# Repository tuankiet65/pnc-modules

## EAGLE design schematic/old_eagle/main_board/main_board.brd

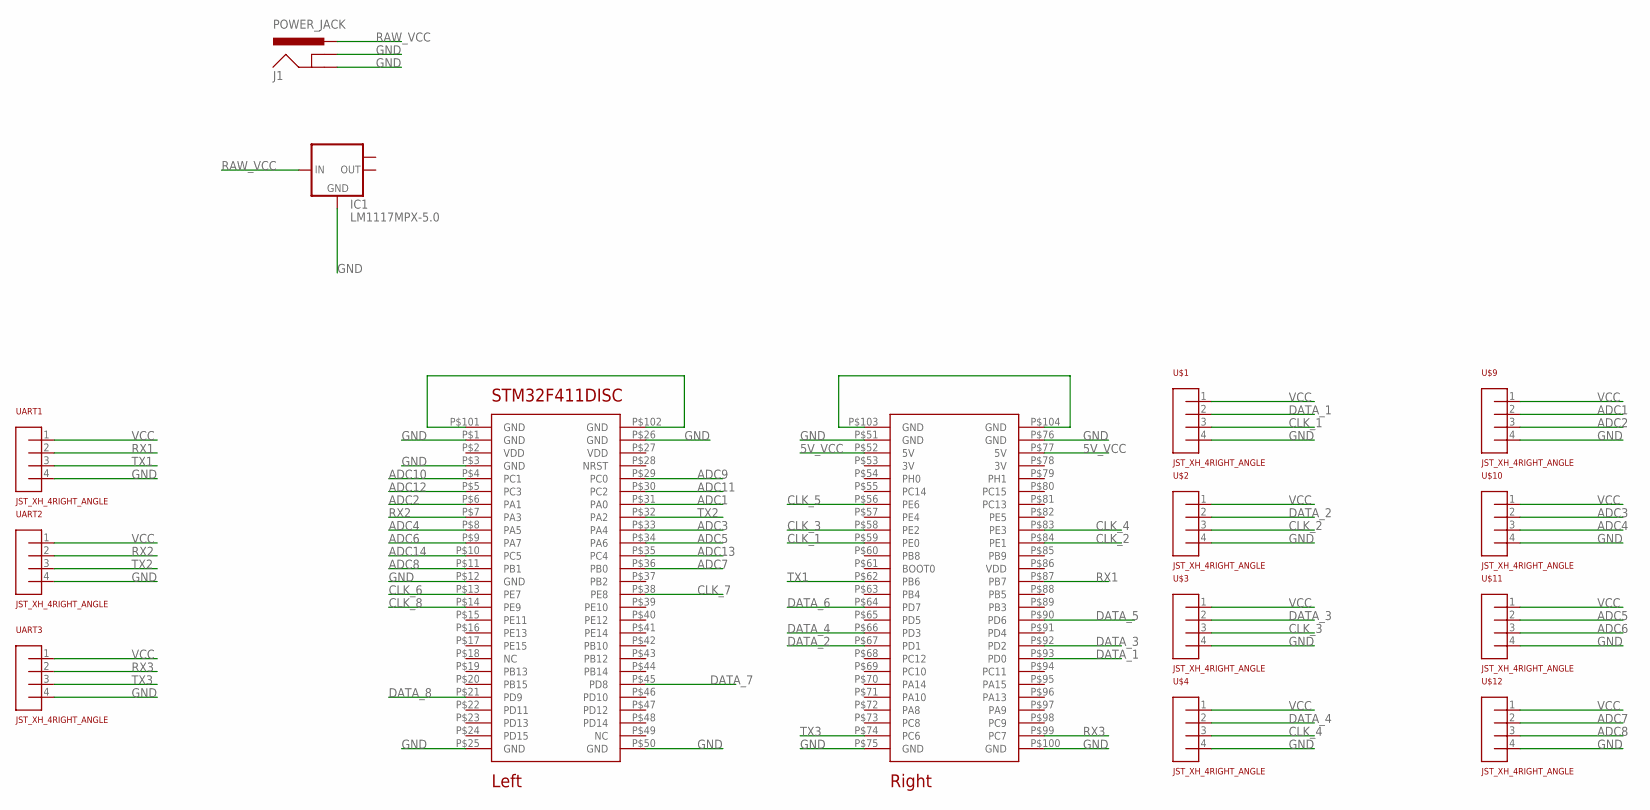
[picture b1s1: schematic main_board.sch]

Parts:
IC1: LM1117MPX-5.0; SOT223
J1: POWER_JACK; POWER_JACK_PTH
STM32F411DISC: STM32F411_DISCOVERY
U$1, U$2, U$3, U$4, U$9, U$10, U$11, U$12: JST_XH_4RIGHT_ANGLE; JST_XH_4PIN_RIGHT_ANGLE
UART1, UART2, UART3: JST_XH_4RIGHT_ANGLE; JST_XH_4PIN_RIGHT_ANGLE

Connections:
5V_VCC: STM32F411DISC.P$52 (5V), STM32F411DISC.P$77 (5V)
ADC1: STM32F411DISC.P$31 (PA0), U$9.2
ADC2: STM32F411DISC.P$6 (PA1), U$9.3
ADC3: STM32F411DISC.P$33 (PA4), U$10.2
ADC4: STM32F411DISC.P$8 (PA5), U$10.3
ADC5: STM32F411DISC.P$34 (PA6), U$11.2
ADC6: STM32F411DISC.P$9 (PA7), U$11.3
ADC7: STM32F411DISC.P$36 (PB0), U$12.2
ADC8: STM32F411DISC.P$11 (PB1), U$12.3
ADC9: STM32F411DISC.P$29 (PC0)
ADC10: STM32F411DISC.P$4 (PC1)
ADC11: STM32F411DISC.P$30 (PC2)
ADC12: STM32F411DISC.P$5 (PC3)
ADC13: STM32F411DISC.P$35 (PC4)
ADC14: STM32F411DISC.P$10 (PC5)
CLK_1: STM32F411DISC.P$59 (PE0), U$1.3
CLK_2: STM32F411DISC.P$84 (PE1), U$2.3
CLK_3: STM32F411DISC.P$58 (PE2), U$3.3
CLK_4: STM32F411DISC.P$83 (PE3), U$4.3
CLK_5: STM32F411DISC.P$56 (PE6)
CLK_6: STM32F411DISC.P$13 (PE7)
CLK_7: STM32F411DISC.P$38 (PE8)
CLK_8: STM32F411DISC.P$14 (PE9)
DATA_1: STM32F411DISC.P$93 (PD0), U$1.2
DATA_2: STM32F411DISC.P$67 (PD1), U$2.2
DATA_3: STM32F411DISC.P$92 (PD2), U$3.2
DATA_4: STM32F411DISC.P$66 (PD3), U$4.2
DATA_5: STM32F411DISC.P$90 (PD6)
DATA_6: STM32F411DISC.P$64 (PD7)
DATA_7: STM32F411DISC.P$45 (PD8)
DATA_8: STM32F411DISC.P$21 (PD9)
GND: IC1.1 (GND), J1.GND, J1.GNDBREAK, STM32F411DISC.P$1 (GND), STM32F411DISC.P$3 (GND), STM32F411DISC.P$12 (GND), STM32F411DISC.P$25 (GND), STM32F411DISC.P$26 (GND), STM32F411DISC.P$50 (GND), STM32F411DISC.P$51 (GND), STM32F411DISC.P$75 (GND), STM32F411DISC.P$76 (GND), STM32F411DISC.P$100 (GND), U$1.4, U$2.4, U$3.4, U$4.4, U$9.4, U$10.4, U$11.4, U$12.4, UART1.4, UART2.4, UART3.4
unnamed: STM32F411DISC.P$103 (GND), STM32F411DISC.P$104 (GND)
unnamed: STM32F411DISC.P$101 (GND), STM32F411DISC.P$102 (GND)
RAW_VCC: IC1.3 (IN), J1.PWR
RX1: STM32F411DISC.P$87 (PB7), UART1.2
RX2: STM32F411DISC.P$7 (PA3), UART2.2
RX3: STM32F411DISC.P$99 (PC7), UART3.2
TX1: STM32F411DISC.P$62 (PB6), UART1.3
TX2: STM32F411DISC.P$32 (PA2), UART2.3
TX3: STM32F411DISC.P$74 (PC6), UART3.3
VCC: U$1.1, U$2.1, U$3.1, U$4.1, U$9.1, U$10.1, U$11.1, U$12.1, UART1.1, UART2.1, UART3.1

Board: 2 copper layers, 14 parts (0 on the bottom side), 28 nets, no tracks yet.

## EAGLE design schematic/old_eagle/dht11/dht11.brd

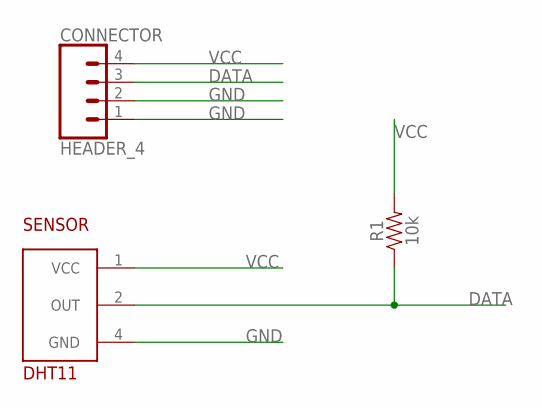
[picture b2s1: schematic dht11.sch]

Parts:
CONNECTOR: HEADER_4; MOLEX-1X4
R1: 10k; AXIAL-0.3
SENSOR: DHT11

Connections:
DATA: CONNECTOR.3, R1.P$1 (1), SENSOR.2 (OUT)
GND: CONNECTOR.1, CONNECTOR.2, SENSOR.4 (GND)
VCC: CONNECTOR.4, R1.P$2 (2), SENSOR.1 (VCC)

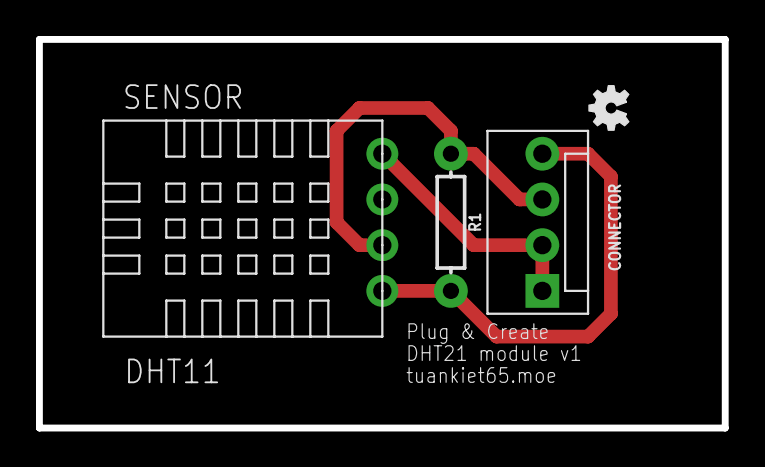
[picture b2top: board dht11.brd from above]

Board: 2 copper layers, 38.1 x 21.6 mm, 4 parts (0 on the bottom side), 3 nets.

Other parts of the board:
U$1: OSHW-LOGO-MINI

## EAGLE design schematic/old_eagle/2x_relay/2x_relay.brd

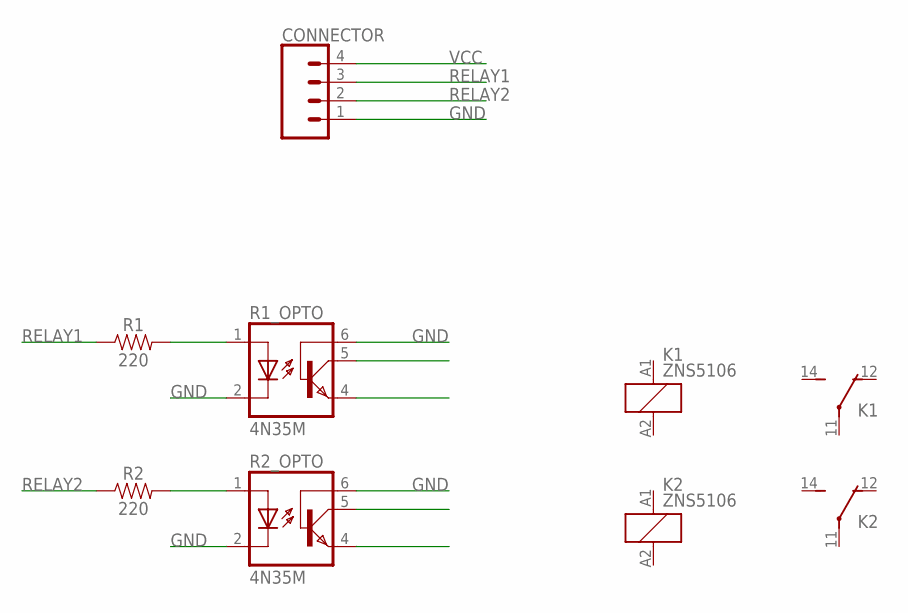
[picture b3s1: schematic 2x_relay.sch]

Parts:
CONNECTOR: CONN_04POLAR; MOLEX-1X4
K1, K2: ZNS5106; ZN5
R1, R2: 220; AXIAL-0.3
R1_OPTO, R2_OPTO: 4N35M; DIL06

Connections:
GND: CONNECTOR.1, R1_OPTO.2 (C), R1_OPTO.6 (BAS), R2_OPTO.2 (C), R2_OPTO.6 (BAS)
unnamed: R1.P$2 (2), R1_OPTO.1 (A)
unnamed: R2.P$2 (2), R2_OPTO.1 (A)
RELAY1: CONNECTOR.3, R1.P$1 (1)
RELAY2: CONNECTOR.2, R2.P$1 (1)
VCC: CONNECTOR.4

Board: 2 copper layers, 7 parts (0 on the bottom side), 5 nets, no tracks yet.

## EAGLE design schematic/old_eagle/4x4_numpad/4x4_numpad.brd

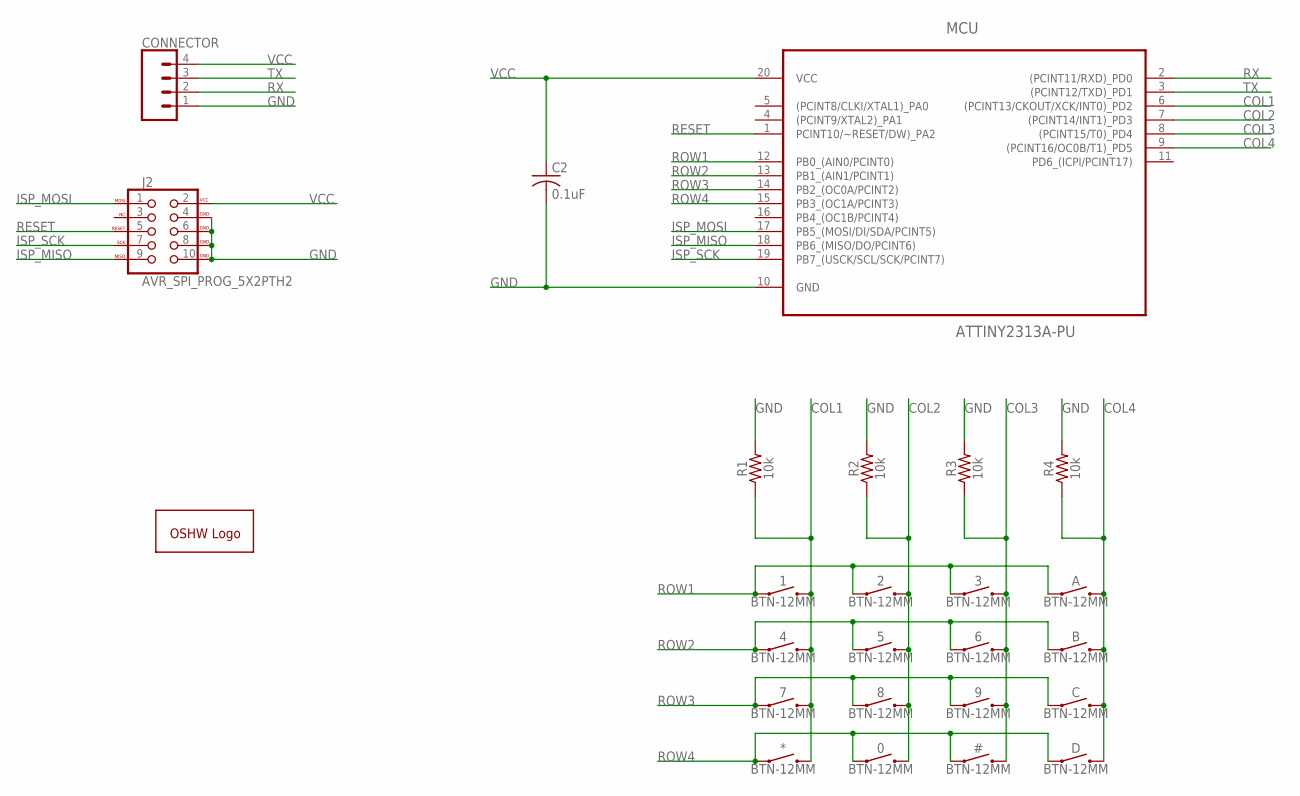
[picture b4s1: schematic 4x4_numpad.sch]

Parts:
0, 1, 2, 3, 4, 5, 6, 7, 8, 9: BTN-12MM; TACTILE_SWITCH_PTH_12MM
#: BTN-12MM; TACTILE_SWITCH_PTH_12MM
*: BTN-12MM; TACTILE_SWITCH_PTH_12MM
A: BTN-12MM; TACTILE_SWITCH_PTH_12MM
B: BTN-12MM; TACTILE_SWITCH_PTH_12MM
C: BTN-12MM; TACTILE_SWITCH_PTH_12MM
C2: 0.1uF; C050-025X075
CONNECTOR: CONN_04; 1X04
D: BTN-12MM; TACTILE_SWITCH_PTH_12MM
GOLD_ORB_SM1: OSHWLOGOLOGO8MM; OSHW_8MM
J2: AVR_SPI_PROG_5X2PTH2; 2X5-SHROUDED
MCU: ATTINY2313A-PU; DIP254P762X533-20
R1, R2, R3, R4: 10k; AXIAL-0.3

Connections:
COL1: 1.3 (2), 1.4 (2), 4.3 (2), 4.4 (2), 7.3 (2), 7.4 (2), *.3 (2), *.4 (2), MCU.6 ((PCINT13/CKOUT/XCK/INT0)_PD2), R1.P$1 (1)
COL2: 0.3 (2), 0.4 (2), 2.3 (2), 2.4 (2), 5.3 (2), 5.4 (2), 8.3 (2), 8.4 (2), MCU.7 ((PCINT14/INT1)_PD3), R2.P$1 (1)
COL3: 3.3 (2), 3.4 (2), 6.3 (2), 6.4 (2), 9.3 (2), 9.4 (2), #.3 (2), #.4 (2), MCU.8 ((PCINT15/T0)_PD4), R3.P$1 (1)
COL4: A.3 (2), A.4 (2), B.3 (2), B.4 (2), C.3 (2), C.4 (2), D.3 (2), D.4 (2), MCU.9 ((PCINT16/OC0B/T1)_PD5), R4.P$1 (1)
GND: C2.2, CONNECTOR.1, J2.4 (GND), J2.6 (GND), J2.8 (GND), J2.10 (GND), MCU.10 (GND), R1.P$2 (2), R2.P$2 (2), R3.P$2 (2), R4.P$2 (2)
ISP_MISO: J2.9 (MISO), MCU.18 (PB6_(MISO/DO/PCINT6))
ISP_MOSI: J2.1 (MOSI), MCU.17 (PB5_(MOSI/DI/SDA/PCINT5))
ISP_SCK: J2.7 (SCK), MCU.19 (PB7_(USCK/SCL/SCK/PCINT7))
RESET: J2.5 (RESET), MCU.1 (PCINT10/~RESET/DW)_PA2)
ROW1: 1.1, 1.2 (1), 2.1, 2.2 (1), 3.1, 3.2 (1), A.1, A.2 (1), MCU.12 (PB0_(AIN0/PCINT0))
ROW2: 4.1, 4.2 (1), 5.1, 5.2 (1), 6.1, 6.2 (1), B.1, B.2 (1), MCU.13 (PB1_(AIN1/PCINT1))
ROW3: 7.1, 7.2 (1), 8.1, 8.2 (1), 9.1, 9.2 (1), C.1, C.2 (1), MCU.14 (PB2_(OC0A/PCINT2))
ROW4: 0.1, 0.2 (1), #.1, #.2 (1), *.1, *.2 (1), D.1, D.2 (1), MCU.15 (PB3_(OC1A/PCINT3))
RX: CONNECTOR.2, MCU.2 ((PCINT11/RXD)_PD0)
TX: CONNECTOR.3, MCU.3 ((PCINT12/TXD)_PD1)
VCC: C2.1, CONNECTOR.4, J2.2 (VCC), MCU.20 (VCC)

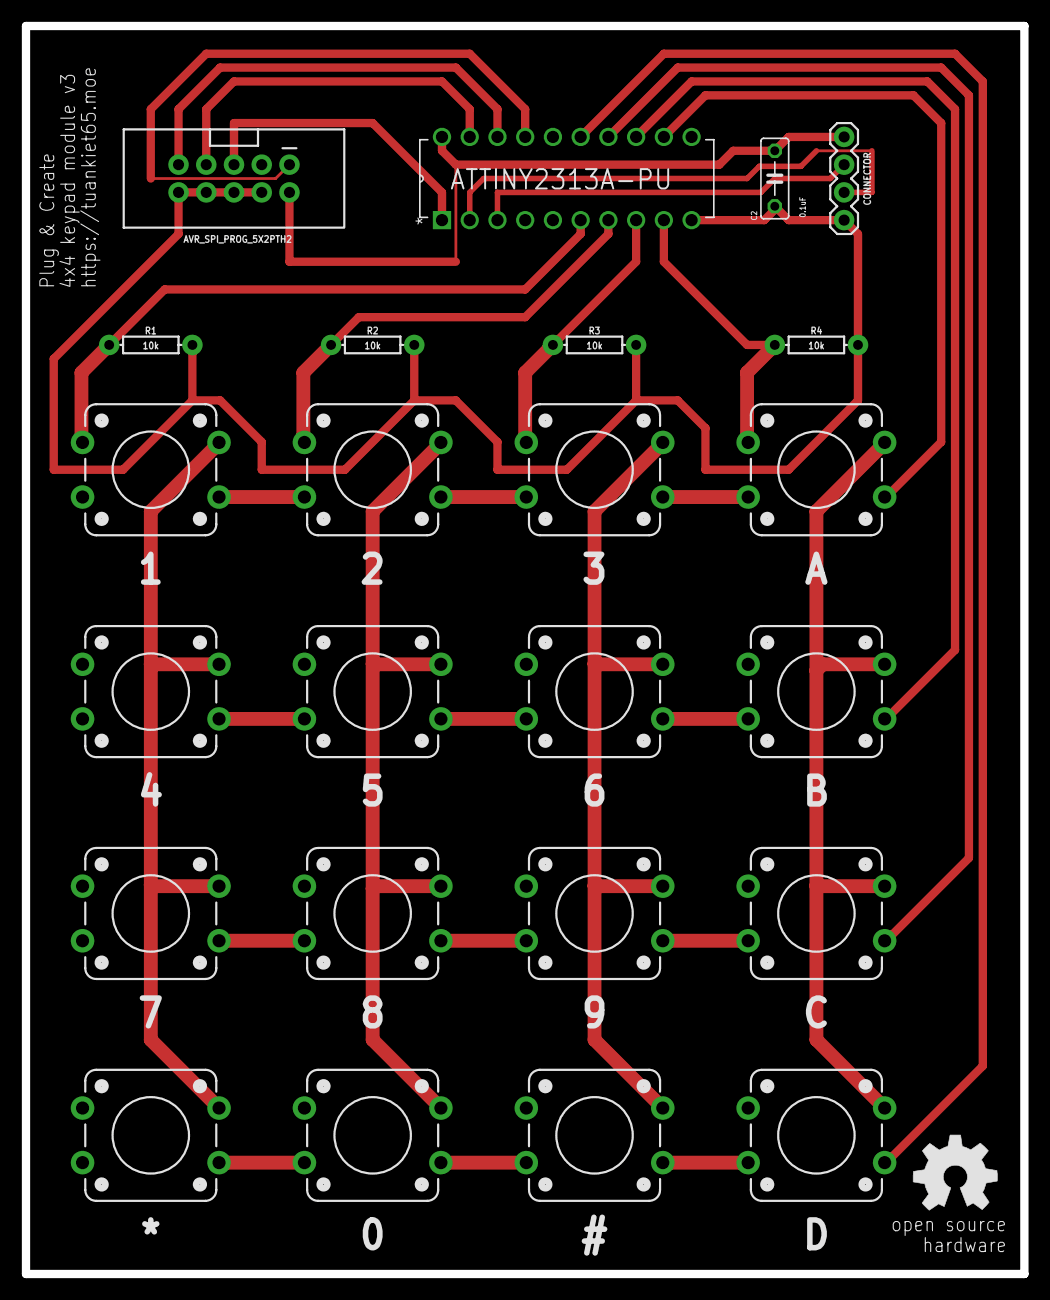
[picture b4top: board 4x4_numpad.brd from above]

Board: 2 copper layers, 91.4 x 114.3 mm, 25 parts (0 on the bottom side), 16 nets.

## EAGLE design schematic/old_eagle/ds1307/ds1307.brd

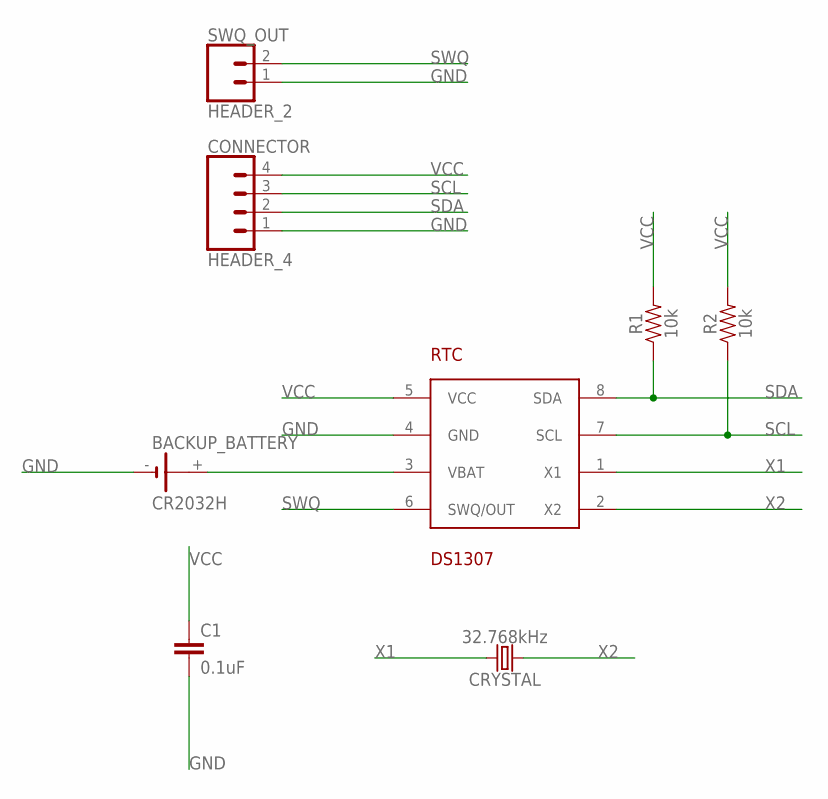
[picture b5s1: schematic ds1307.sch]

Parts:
BACKUP_BATTERY: CR2032H
C1: 0.1uF; CAP-PTH-SMALL-KIT
CONNECTOR: HEADER_4; MOLEX-1X4
CRYSTAL: 32.768kHz; CRYSTAL-PTH-2X6-CYL
R1, R2: 10k; AXIAL-0.3
RTC: DS1307; MAXIM_DIP8
SWQ_OUT: HEADER_2; 1X02

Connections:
GND: BACKUP_BATTERY.-, C1.2, CONNECTOR.1, RTC.4 (GND), SWQ_OUT.1
unnamed: BACKUP_BATTERY.+, RTC.3 (VBAT)
SCL: CONNECTOR.3, R2.P$1 (1), RTC.7 (SCL)
SDA: CONNECTOR.2, R1.P$1 (1), RTC.8 (SDA)
SWQ: RTC.6 (SWQ/OUT), SWQ_OUT.2
VCC: C1.1, CONNECTOR.4, R1.P$2 (2), R2.P$2 (2), RTC.5 (VCC)
X1: CRYSTAL.2, RTC.1 (X1)
X2: CRYSTAL.1, RTC.2 (X2)

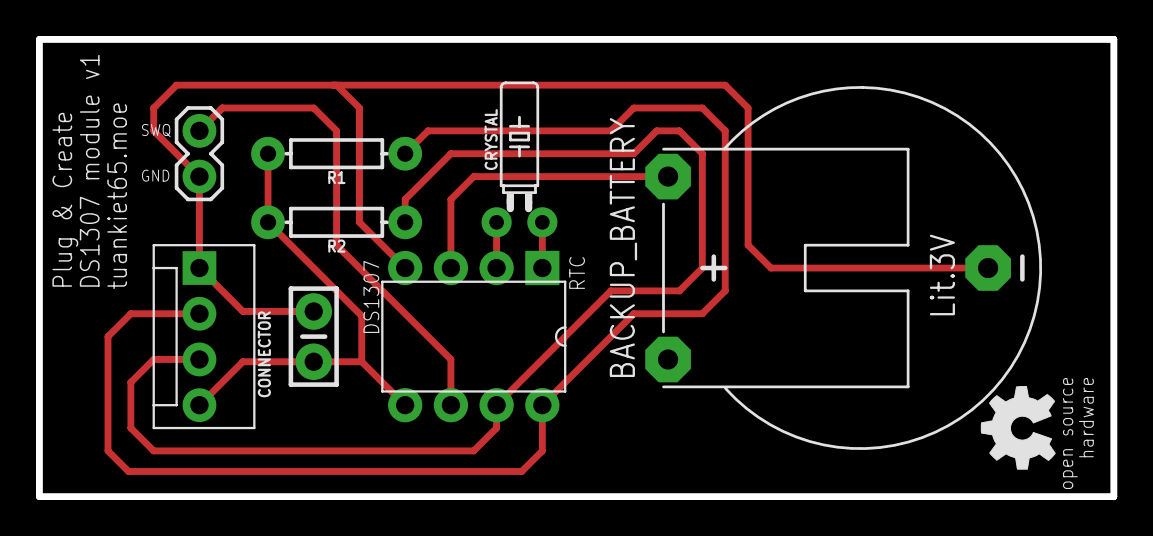
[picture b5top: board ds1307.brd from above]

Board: 2 copper layers, 59.7 x 25.4 mm, 9 parts (0 on the bottom side), 8 nets.

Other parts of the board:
U$1: OSHW_5MM

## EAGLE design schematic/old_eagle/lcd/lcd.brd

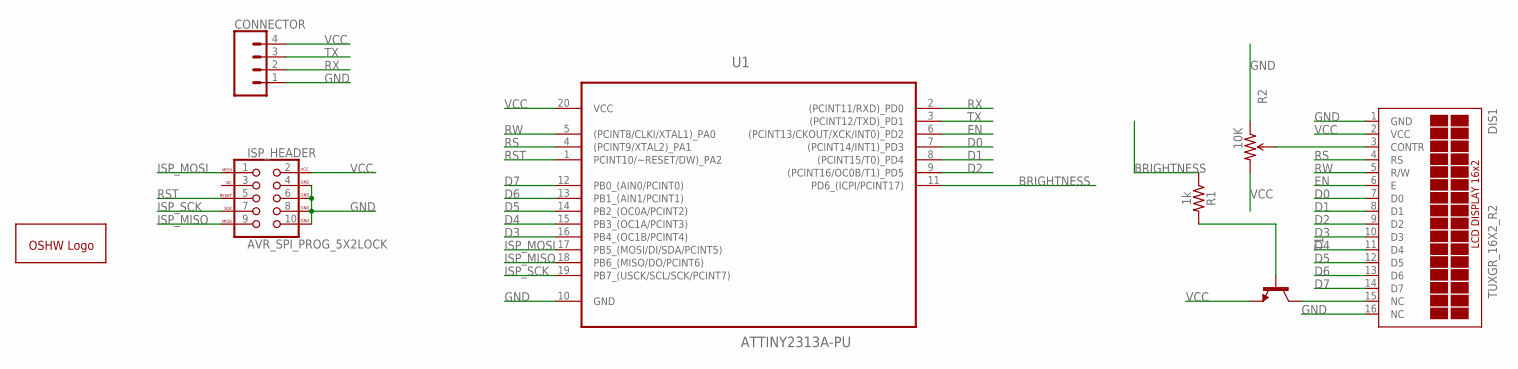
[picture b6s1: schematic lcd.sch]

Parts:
CONNECTOR: CONN_04; 1X04
DIS1: TUXGR_16X2_R2
GOLD_ORB_SM2: OSHWLOGOLOGO5MM; OSHW_5MM
ISP_HEADER: AVR_SPI_PROG_5X2LOCK; 2X5-SHROUDED_LOCK
R1: 1k; AXIAL-0.3
R2: 10K; TRIM_POT_PTH
T1: -NPN-TO92-ECB; TO92-ECB
U1: ATTINY2313A-PU; DIP254P762X533-20

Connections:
BRIGHTNESS: R1.P$1 (1), U1.11 (PD6_(ICPI/PCINT17))
CONTRAST: DIS1.3 (CONTR), R2.2 (WIPER)
D0: DIS1.7 (D0), U1.7 ((PCINT14/INT1)_PD3)
D1: DIS1.8 (D1), U1.8 ((PCINT15/T0)_PD4)
D2: DIS1.9 (D2), U1.9 ((PCINT16/OC0B/T1)_PD5)
D3: DIS1.10 (D3), U1.16 (PB4_(OC1B/PCINT4))
D4: DIS1.11 (D4), U1.15 (PB3_(OC1A/PCINT3))
D5: DIS1.12 (D5), U1.14 (PB2_(OC0A/PCINT2))
D6: DIS1.13 (D6), U1.13 (PB1_(AIN1/PCINT1))
D7: DIS1.14 (D7), U1.12 (PB0_(AIN0/PCINT0))
EN: DIS1.6 (E), U1.6 ((PCINT13/CKOUT/XCK/INT0)_PD2)
GND: CONNECTOR.1, DIS1.1 (GND), DIS1.16 (NC), ISP_HEADER.4 (GND), ISP_HEADER.6 (GND), ISP_HEADER.8 (GND), ISP_HEADER.10 (GND), R2.1 (CCW), U1.10 (GND)
ISP_MISO: ISP_HEADER.9 (MISO), U1.18 (PB6_(MISO/DO/PCINT6))
ISP_MOSI: ISP_HEADER.1 (MOSI), U1.17 (PB5_(MOSI/DI/SDA/PCINT5))
ISP_SCK: ISP_HEADER.7 (SCK), U1.19 (PB7_(USCK/SCL/SCK/PCINT7))
unnamed: DIS1.15 (NC), T1.C
unnamed: R1.P$2 (2), T1.B
RS: DIS1.4 (RS), U1.4 ((PCINT9/XTAL2)_PA1)
RST: ISP_HEADER.5 (RESET), U1.1 (PCINT10/~RESET/DW)_PA2)
RW: DIS1.5 (R/W), U1.5 ((PCINT8/CLKI/XTAL1)_PA0)
RX: CONNECTOR.2, U1.2 ((PCINT11/RXD)_PD0)
TX: CONNECTOR.3, U1.3 ((PCINT12/TXD)_PD1)
VCC: CONNECTOR.4, DIS1.2 (VCC), ISP_HEADER.2 (VCC), R2.3 (CW), T1.E, U1.20 (VCC)

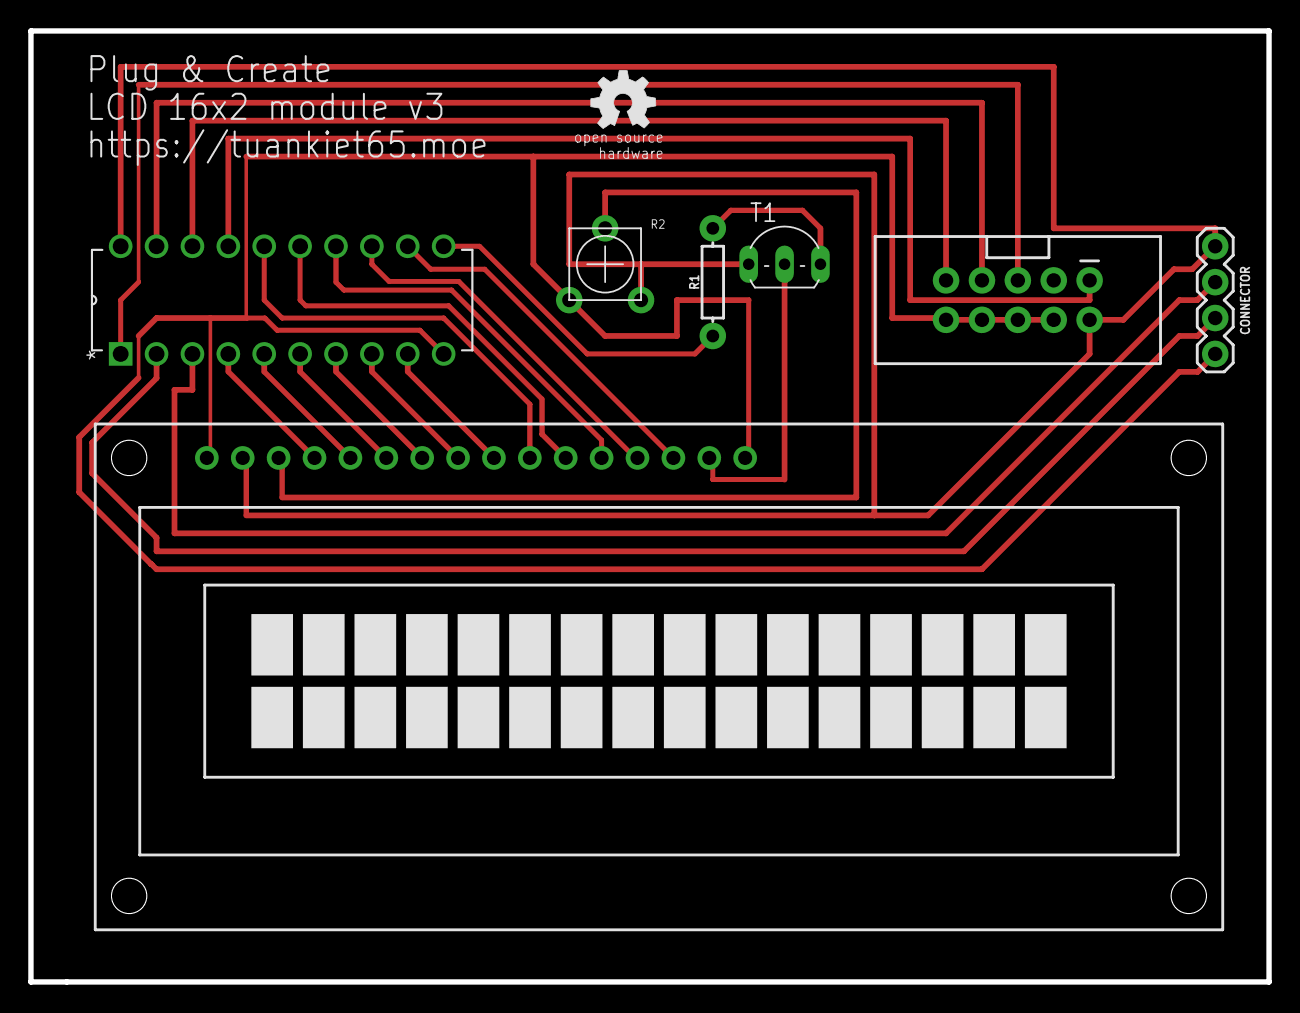
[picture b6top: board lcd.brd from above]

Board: 2 copper layers, 87.6 x 67.3 mm, 8 parts (0 on the bottom side), 23 nets.

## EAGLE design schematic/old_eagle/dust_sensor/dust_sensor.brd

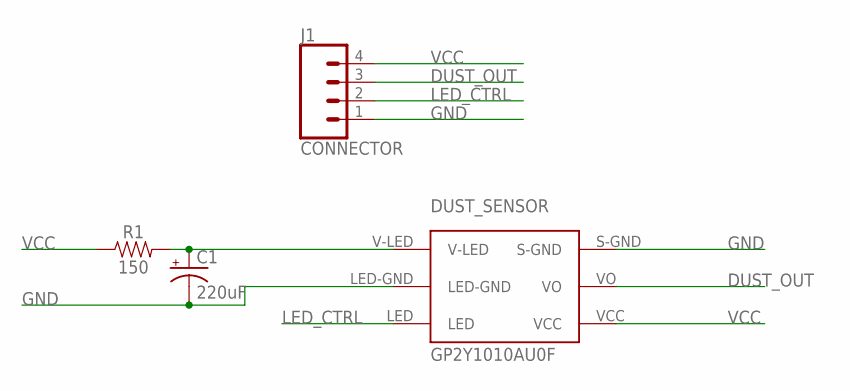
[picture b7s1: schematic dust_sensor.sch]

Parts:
C1: 220uF; E2,5-6
DUST_SENSOR: GP2Y1010AU0F
J1: CONNECTOR; MOLEX-1X4
R1: 150; AXIAL-0.3

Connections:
DUST_OUT: DUST_SENSOR.VO, J1.3
GND: C1.-, DUST_SENSOR.LED-GND, DUST_SENSOR.S-GND, J1.1
LED_CTRL: DUST_SENSOR.LED, J1.2
unnamed: C1.+, DUST_SENSOR.V-LED, R1.P$2 (2)
VCC: DUST_SENSOR.VCC, J1.4, R1.P$1 (1)

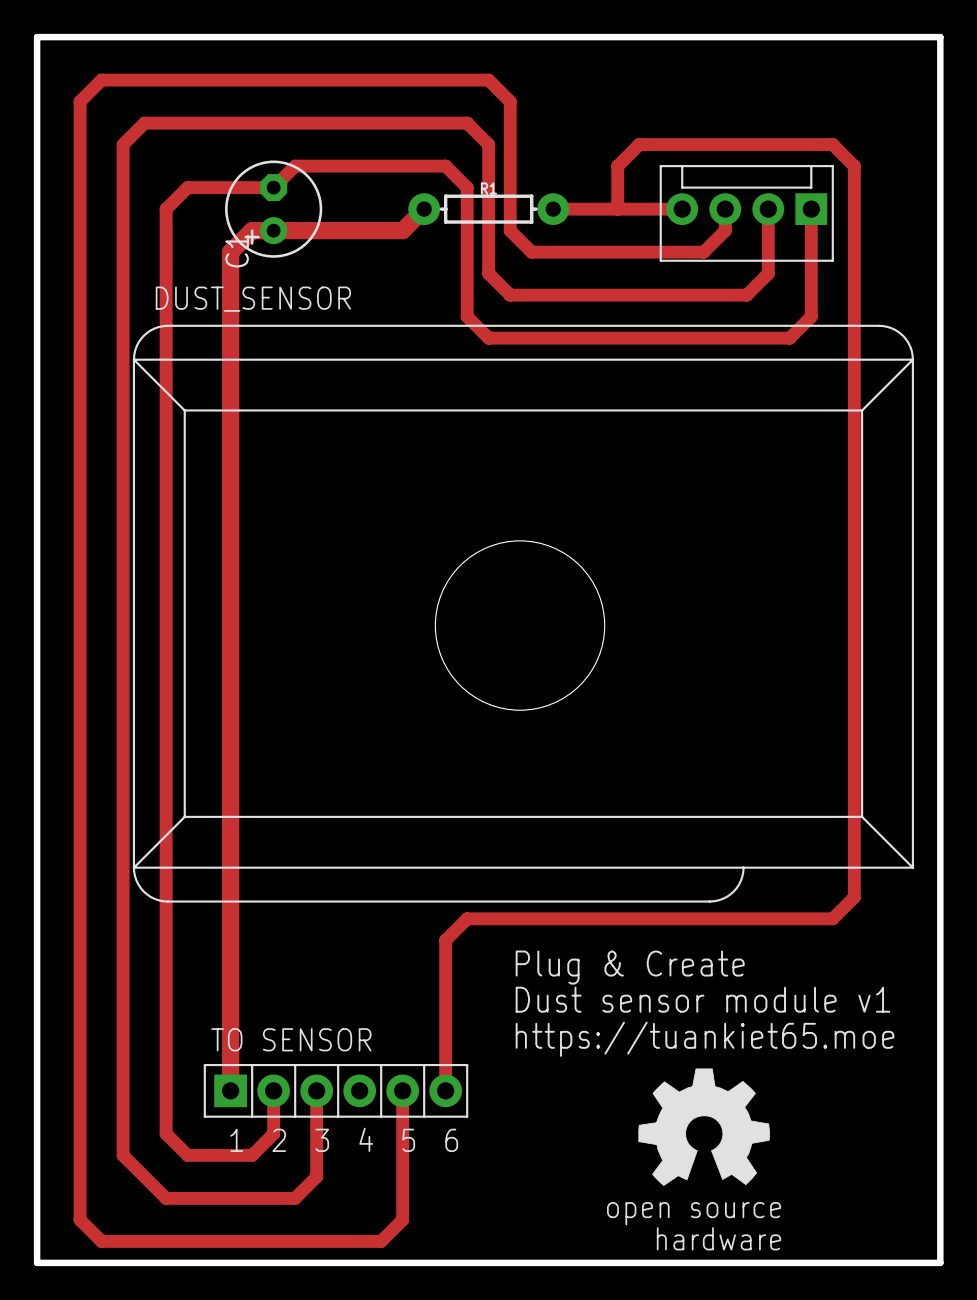
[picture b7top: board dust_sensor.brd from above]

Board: 2 copper layers, 53.3 x 72.4 mm, 5 parts (0 on the bottom side), 5 nets.

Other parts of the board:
U$1: OSHW_8MM

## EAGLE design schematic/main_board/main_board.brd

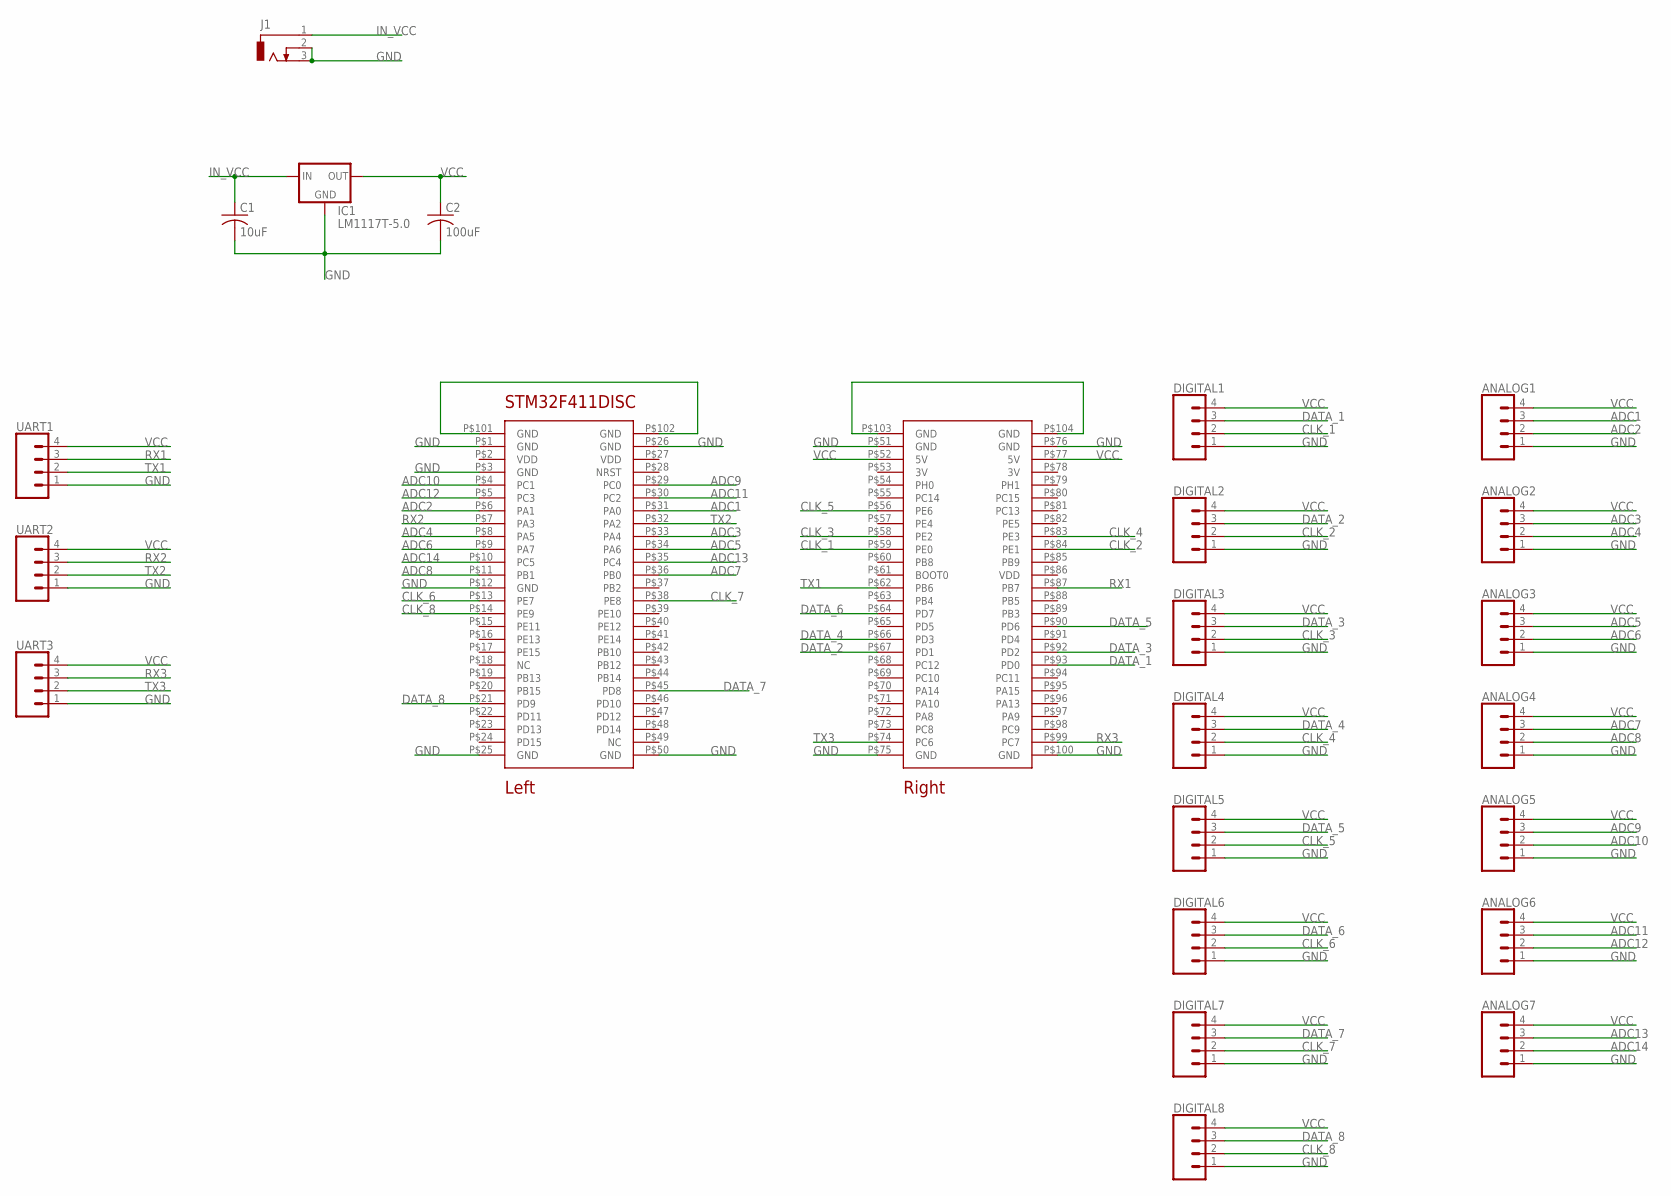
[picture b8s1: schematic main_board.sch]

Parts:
ANALOG1, ANALOG2, ANALOG3, ANALOG4, ANALOG5, ANALOG6, ANALOG7: CONN_04; 1X04
C1: 10uF; C025-025X050
C2: 100uF; C025-025X050
DIGITAL1, DIGITAL2, DIGITAL3, DIGITAL4, DIGITAL5, DIGITAL6, DIGITAL7, DIGITAL8: CONN_04; 1X04
IC1: LM1117T-5.0; TO220
J1: DCJ0303
STM32F411DISC: STM32F411_DISCOVERY
UART1, UART2, UART3: CONN_04; 1X04

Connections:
ADC1: ANALOG1.3, STM32F411DISC.P$31 (PA0)
ADC2: ANALOG1.2, STM32F411DISC.P$6 (PA1)
ADC3: ANALOG2.3, STM32F411DISC.P$33 (PA4)
ADC4: ANALOG2.2, STM32F411DISC.P$8 (PA5)
ADC5: ANALOG3.3, STM32F411DISC.P$34 (PA6)
ADC6: ANALOG3.2, STM32F411DISC.P$9 (PA7)
ADC7: ANALOG4.3, STM32F411DISC.P$36 (PB0)
ADC8: ANALOG4.2, STM32F411DISC.P$11 (PB1)
ADC9: ANALOG5.3, STM32F411DISC.P$29 (PC0)
ADC10: ANALOG5.2, STM32F411DISC.P$4 (PC1)
ADC11: ANALOG6.3, STM32F411DISC.P$30 (PC2)
ADC12: ANALOG6.2, STM32F411DISC.P$5 (PC3)
ADC13: ANALOG7.3, STM32F411DISC.P$35 (PC4)
ADC14: ANALOG7.2, STM32F411DISC.P$10 (PC5)
CLK_1: DIGITAL1.2, STM32F411DISC.P$59 (PE0)
CLK_2: DIGITAL2.2, STM32F411DISC.P$84 (PE1)
CLK_3: DIGITAL3.2, STM32F411DISC.P$58 (PE2)
CLK_4: DIGITAL4.2, STM32F411DISC.P$83 (PE3)
CLK_5: DIGITAL5.2, STM32F411DISC.P$56 (PE6)
CLK_6: DIGITAL6.2, STM32F411DISC.P$13 (PE7)
CLK_7: DIGITAL7.2, STM32F411DISC.P$38 (PE8)
CLK_8: DIGITAL8.2, STM32F411DISC.P$14 (PE9)
DATA_1: DIGITAL1.3, STM32F411DISC.P$93 (PD0)
DATA_2: DIGITAL2.3, STM32F411DISC.P$67 (PD1)
DATA_3: DIGITAL3.3, STM32F411DISC.P$92 (PD2)
DATA_4: DIGITAL4.3, STM32F411DISC.P$66 (PD3)
DATA_5: DIGITAL5.3, STM32F411DISC.P$90 (PD6)
DATA_6: DIGITAL6.3, STM32F411DISC.P$64 (PD7)
DATA_7: DIGITAL7.3, STM32F411DISC.P$45 (PD8)
DATA_8: DIGITAL8.3, STM32F411DISC.P$21 (PD9)
GND: ANALOG1.1, ANALOG2.1, ANALOG3.1, ANALOG4.1, ANALOG5.1, ANALOG6.1, ANALOG7.1, C1.2, C2.2, DIGITAL1.1, DIGITAL2.1, DIGITAL3.1, DIGITAL4.1, DIGITAL5.1, DIGITAL6.1, DIGITAL7.1, DIGITAL8.1, IC1.1 (GND), J1.2, J1.3, STM32F411DISC.P$1 (GND), STM32F411DISC.P$3 (GND), STM32F411DISC.P$12 (GND), STM32F411DISC.P$25 (GND), STM32F411DISC.P$26 (GND), STM32F411DISC.P$50 (GND), STM32F411DISC.P$51 (GND), STM32F411DISC.P$75 (GND), STM32F411DISC.P$76 (GND), STM32F411DISC.P$100 (GND), UART1.1, UART2.1, UART3.1
IN_VCC: C1.1, IC1.3 (IN), J1.1
unnamed: STM32F411DISC.P$103 (GND), STM32F411DISC.P$104 (GND)
unnamed: STM32F411DISC.P$101 (GND), STM32F411DISC.P$102 (GND)
RX1: STM32F411DISC.P$87 (PB7), UART1.3
RX2: STM32F411DISC.P$7 (PA3), UART2.3
RX3: STM32F411DISC.P$99 (PC7), UART3.3
TX1: STM32F411DISC.P$62 (PB6), UART1.2
TX2: STM32F411DISC.P$32 (PA2), UART2.2
TX3: STM32F411DISC.P$74 (PC6), UART3.2
VCC: ANALOG1.4, ANALOG2.4, ANALOG3.4, ANALOG4.4, ANALOG5.4, ANALOG6.4, ANALOG7.4, C2.1, DIGITAL1.4, DIGITAL2.4, DIGITAL3.4, DIGITAL4.4, DIGITAL5.4, DIGITAL6.4, DIGITAL7.4, DIGITAL8.4, IC1.2 (OUT), STM32F411DISC.P$52 (5V), STM32F411DISC.P$77 (5V), UART1.4, UART2.4, UART3.4

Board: 2 copper layers, 23 parts (3 on the bottom side), 41 nets, no tracks yet.

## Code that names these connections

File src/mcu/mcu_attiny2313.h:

#ifndef MCU_ATTINY2313_H

	#define MCU_ATTINY2313_H
	
	volatile uint8_t* PIN_DD_REGS[] = {
		&DDRA,   // Port A
		&DDRB,   // Port B
		nullptr, // Port C (not used)
		&DDRD,  // Port D
	};

	volatile uint8_t* PIN_PORT_REGS[] = {
		&PORTA,  // Port A
		&PORTB,  // Port B
		nullptr, // Port C (not used)
		&PORTD,  // Port D
	};

	volatile uint8_t* PIN_PIN_REGS[] = {
		&PINA,   // Port A
		&PINB,   // Port B
		nullptr, // Port C (not used)
		&PIND,   // Port D
	};

	#define PIN_PA0 0b00000000
	#define PIN_PA1 0b00000001
	#define PIN_PA2 0b00000010
	#define PIN_PB0 0b00001000
	#define PIN_PB1 0b00001001
	#define PIN_PB2 0b00001010
	#define PIN_PB3 0b00001011
	#define PIN_PB4 0b00001100
	#define PIN_PB5 0b00001101
	#define PIN_PB6 0b00001110
	#define PIN_PB7 0b00001111
	#define PIN_PD0 0b00011000
	#define PIN_PD1 0b00011001
	#define PIN_PD2 0b00011010
	#define PIN_PD3 0b00011011
	#define PIN_PD4 0b00011100
	#define PIN_PD5 0b00011101
	#define PIN_PD6 0b00011110

#endif

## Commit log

2017-06-24 _Serial now reads and writes bytes instead of data_packet
    The work of assembling data_packet is now in the main loop instead of in _Serial
2017-06-25 makefile: do not strip output elf
    There's no need to strip output binary as all symbols are ignored by avr-objcopy
2017-06-25 hd44780: new void _pin_write for writing to pins
    Avoid 'don't repeat yourself', also help to reduce code size
2017-06-25 protocol: reduce maximum data size to 8 byte
    8 byte ought be enough for most, and this helps reduce RAM usage
2017-06-25 uart/hard_uart: reduce buffer size to 10 byte
    In 1129d68, sizeof(data_packet) has been reduced to 10 bytes. We reduce the buffer size to accommodate for that change.
2017-06-25 makefile: change executable extension to .elf
    That feels right, also gitignore can ignore .elf extensions
2017-06-25 lcd_16x2_block: change if/then structure to switch/case
2017-06-25 lcd/hd44780: add support for backlight pin
2017-06-25 io: change if/then structure to switch/case
2017-06-28 uart/hard_uart: Enable UDR Ready Interrupt after incrementing tx_buf.tail
    Looks like if we do it before then characters will be lost/delayed.
    Examples:
    while(1){
    Serial.send('A');
    Serial.send('b');
    _delay_ms(1000);
2017-06-28 uart/hard_uart: Don't enable URDIE in initialization
    It will be enabled when the program executes a transmission
2017-06-28 New virtual class: Stream
    Stream is a virtual class for stream-like type (for example Serial)
    (idea copied from Arduino)
2017-06-28 New DataPacketStream class
    DataPackerStream is a Stream-like (although not really inherited from Stream) for packet data
2017-06-28 io: make some operations atomic
2017-06-28 lcd/hd44780: some code/data size optimizations
2017-06-28 lcd_16x2_block: Move to using DataPacketStream
2017-06-28 lcd_hd44780: Move LCD_START_ADDR to PROGMEM
2017-06-28 uart/hard_uart: increase buffer size to 8
    Hopefully we can make it to 10 (but that's unlikely)
2017-06-28 lcd/hd44780: enable brightness control using fake PWM
    "Fake PWM" because in the original schematic, the backlight pin is connected to PD6, which is not a Output Compare pin. As such we abuse the Timer's overflow/compare feature to fake a PWM.
    Due to this change, UART buffer size has to be decreased to 4 to accommodate for this change
2017-08-14 Add new numpad_4x4 module
2017-10-07 Mainboard
2017-10-07 Add PDF schematic
2017-10-07 Add top and bottom layer PDF
2017-10-07 Add top and bottom payer PDF with copper pour
2018-07-04 Committing everything
    Because my hard drive will soon crash and burn.o

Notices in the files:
parts and their libraries:
SparkFun-Resistors: Licensing: Creative Commons ShareAlike 4.0 International - https://creativecommons.org/licenses/by-sa/4.0
